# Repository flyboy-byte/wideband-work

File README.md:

# wideband-work: rusEFI wideband controller with a 0-5 V analog output

> [!NOTE]
> This is a fork of [mck1117/wideband](https://github.com/mck1117/wideband) (MIT) on branch `analog-out`. `master` is
> upstream, untouched. Nothing here has been built or tested on hardware yet. As of 2026-10-24 the carrier board (r41)
> is routed and checked, with JLC fab files exported and verified part by part; an independent audit round and the
> order are still to come. **Reviewing it?** Start at [`REVIEW.md`](REVIEW.md).

This repository is three things at once.

**1. A wideband O2 controller.** It is upstream's open STM32 controller for a Bosch LSU 4.9 sensor plus a 0-5 V analog
output on the carrier board. With that output it works with any ECU or logger that reads a voltage, not only rusEFI
over CAN: Speeduino, a Honda K20 on Hondata FlashPro (datalogging), a gauge for carburettor tuning. The output is
10-20 AFR = 0-5 V, 5 V (off-scale lean) while the sensor isn't ready, buffered from a 3.000 V reference and filtered. The op-amp takes
its feedback at the output pin, so the receiver's input (pull-up or pull-down) doesn't shift the reading, and it stays
stable into cable capacitance; both were checked against TI's op-amp model. The firmware also gains an independent
watchdog on the heater loop, and fixes for three bugs found by host and emulator tests: two inherited from upstream
(bootloader write bounds, a Cortex-M0 fault handler that locked up) and one of ours.

**2. An AI-designed hardware project.** Claude (Anthropic) did the design work from code, with the owner directing it:
- the requirements, parts research against the JLC/LCSC catalogue, and the firmware change
- the schematic (`work/gen/gen_carrier_sch.py`) and the PCB (`work/gen/gen_carrier_pcb.py`, with placement, routing and
  a negotiated router for the dense analog area), all generated
- SPICE checks of the analog stage
- the JLC fab files, with each part's rotation, origin and pin names measured from its EasyEDA footprint (that check
  caught the reverse-polarity diode, which would otherwise have been placed backwards)
- every check that gates an order

Every claim carries an evidence tag (DOCUMENTED / REPORTED / INFERRED / UNKNOWN), and the mistakes it caught are in
`work/LESSONS.md`.

**3. A worked example of a documented workflow.** The project follows the
[`pcb-design` skill](https://github.com/flyboy-byte/scripts-docs-dotfiles/tree/master/skills/pcb-design):
- a stage-gated `STATE.md`
- checks that run together (`work/checks/run_all.py`)
- a money gate (`release.py`) that refuses to copy fab files unless everything passes and an audit is clear
- a drift check for hand edits in KiCad
- attempt logs with results
- a `HANDOFF.md`, so a new session or another model can pick the work up cold

`AGENTS.md` is written for any model; Codex audits go through `work/checks/audit_pack.py`, and the two models take
turns (audit, verify, fix) as `AGENTS.md` describes. Rounds so far are in `work/AUDIT.md`. Outside reviewers (a person,
or their own model) start at [`REVIEW.md`](REVIEW.md): setup from a fresh clone, blind pack or full repo, report format.

## Where to look

| Path | What |
| --- | --- |
| `work/STATE.md` | Current stage, decisions, check results, what's open |
| `work/RELEASE_ASSESSMENT.md` | Plain-language status: what is checked, how independently, the open caveats |
| `work/HANDOFF.md` | Dense hand-off for the next session: run history, last raw output, next steps |
| `work/docs/analog-out.md`, `carrier.md`, `firmware.md` | The design, with sources |
| `work/gen/` | Schematic and PCB generators, the routing finisher |
| `work/checks/` | The checks (`run_all.py`): DRC against upstream's baseline, via-in-pad, layout review, JLC rotation, fab files, firmware tests, drift, release gate |
| `work/gen/export_fab.py` | Gerbers, BOM and CPL for JLC (into `work/out/`, gitignored; only `release.py` puts files in `fab/`) |
| `work/sim/` | ngspice decks: filter, op-amp stability, accuracy into different receiver inputs |
| `firmware/` (branch `analog-out`) | Analog output on PB1 / TIM3_CH4, bench test mode, trim, watchdog |
| `test/` | Upstream's unit tests plus ours (`test/aux_out/` for the analog output) |
| `AGENTS.md`, `CLAUDE.md` | How an AI (any model) works in this repo |

---

*Upstream's README follows.*

# rusEFI Wideband Controller

[User Documentation](https://rusefi.com/s/wb)

[Forum Thread](https://rusefi.com/forum/viewtopic.php?f=4&t=1856)

## Building Firmware

The `firmware/boards` directory contains configuration for each board this firmware supports.

For the standalone board and the module built in to rusEFI Hellen boards, `f0_module` is the correct target.  Use the `build_wideband.sh` script to build and package the wideband firmware: both a bin including the bootloader, and a header file consumed by rusEFI that contains no bootloader, to be uploaded over CAN (via the aforementioned bootloader).

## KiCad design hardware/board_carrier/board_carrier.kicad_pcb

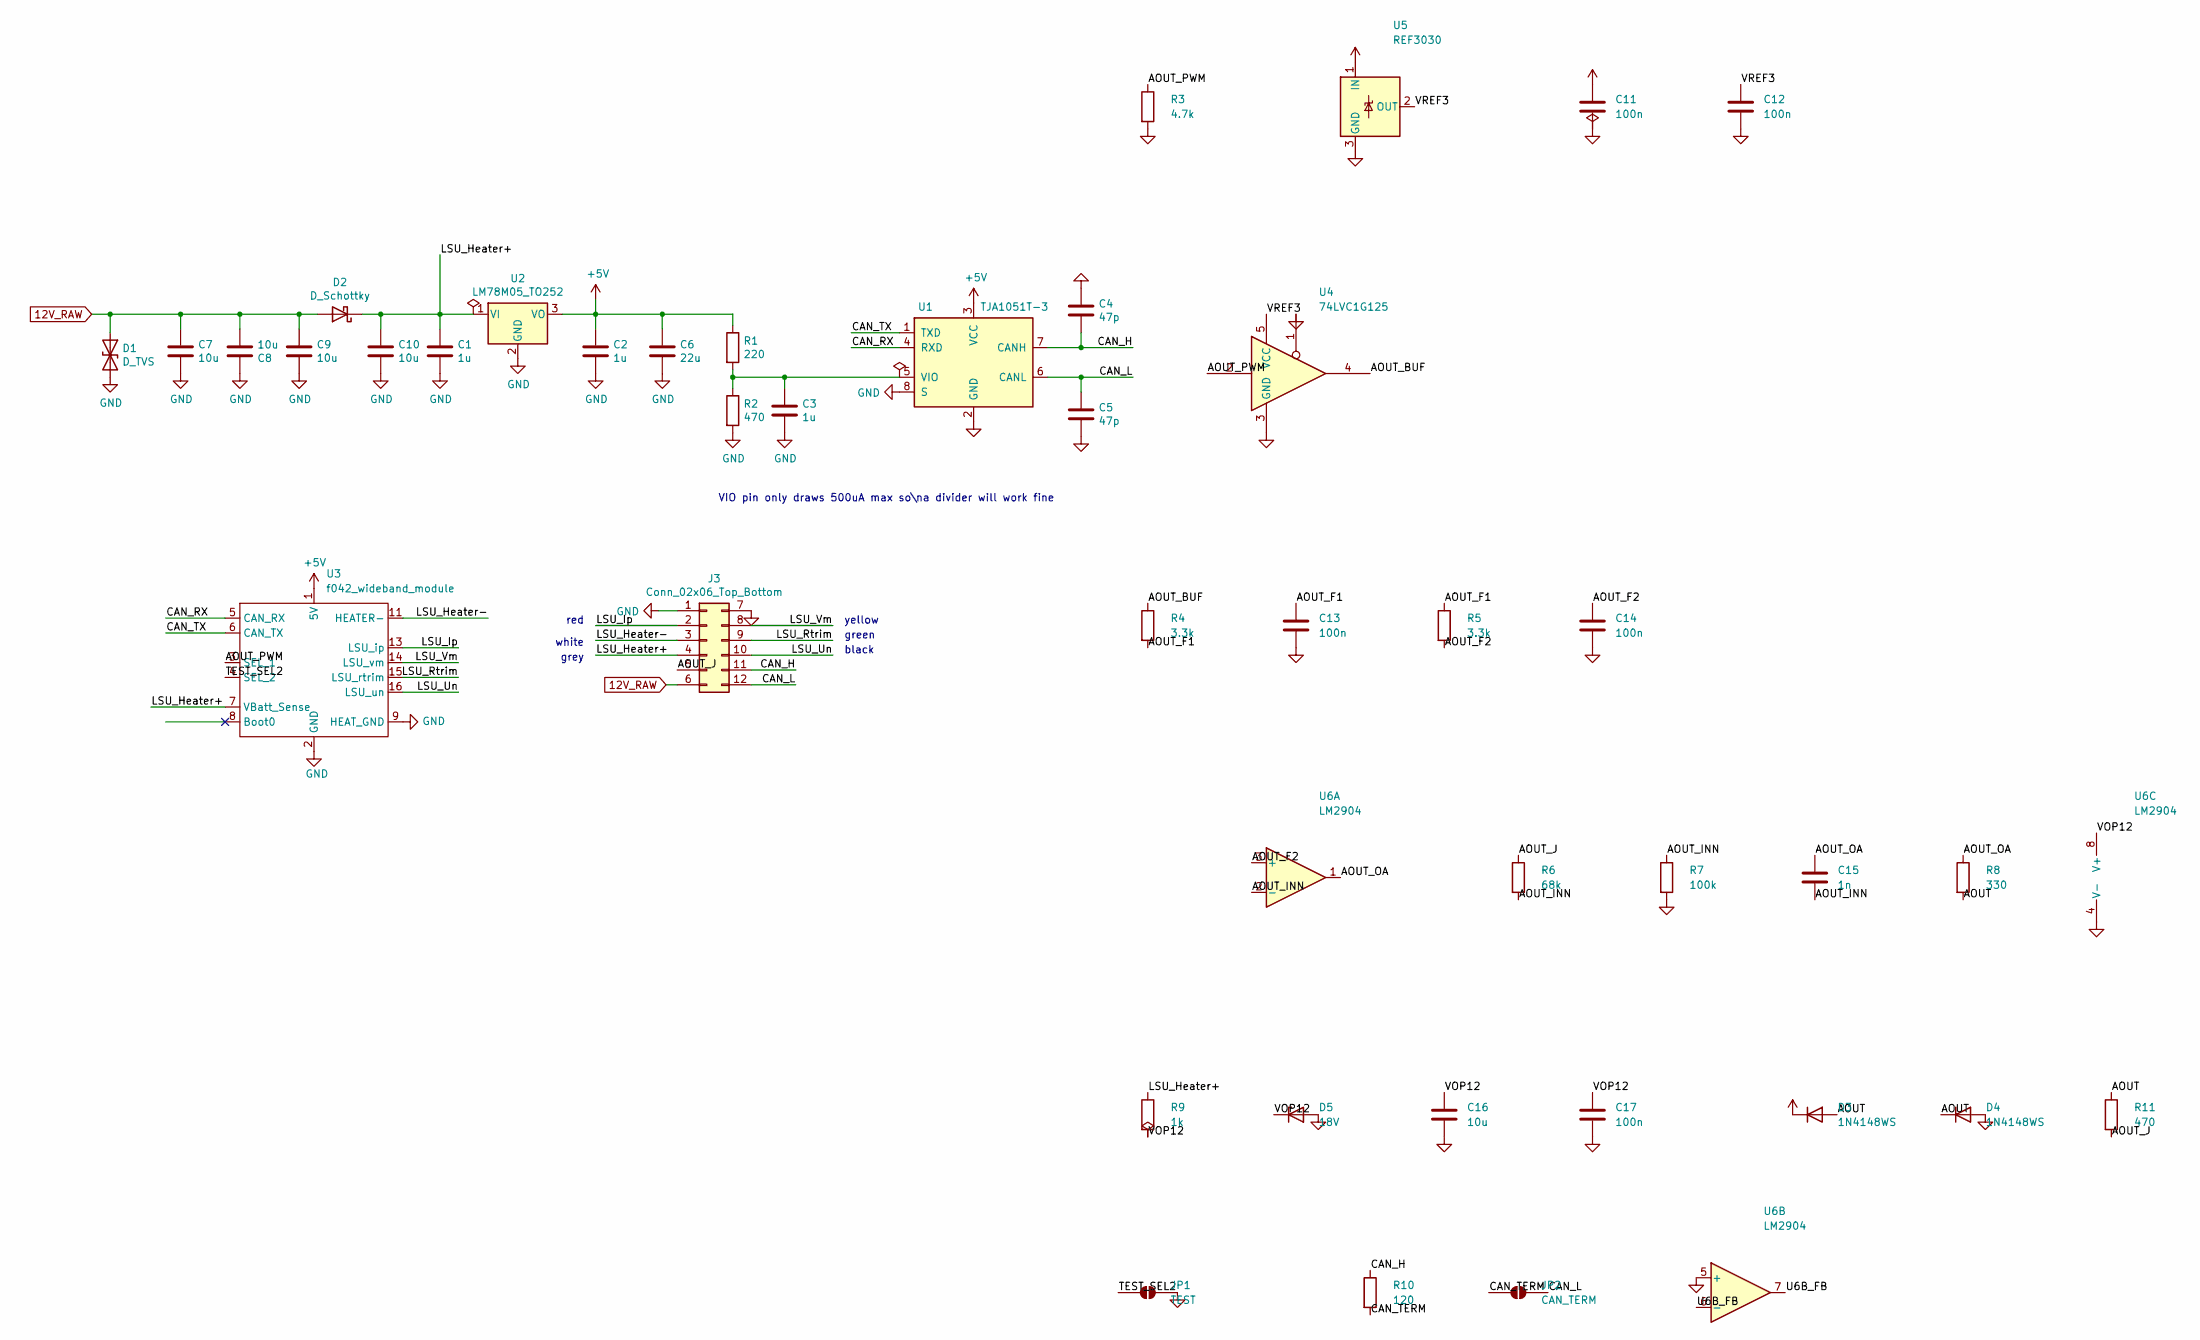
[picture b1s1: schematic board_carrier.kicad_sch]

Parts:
C1, C2, C3: 1u; C_0603_1608Metric; LCSC C15849
C4, C5: 47p; C_0402_1005Metric; LCSC C1567
C6: 22u; C_0805_2012Metric; LCSC C45783
C7, C8, C9, C10, C16: 10u; C_1206_3216Metric; LCSC C13585
C11, C12, C13, C14: 100n; C_0402_1005Metric; LCSC C1525
C15: 1n; C_0402_1005Metric; LCSC C1523
C17: 100n; C_0603_1608Metric; LCSC C14663
D1: D_TVS; D_SMC; LCSC C151279
D2: D_Schottky; D_SMA; LCSC C22452
D3, D4: 1N4148WS; D_SOD-323; LCSC C2128
D5: 18V; D_SOD-123; LCSC C173425
J3: Conn_02x06_Top_Bottom; mx120g-12
JP1: TEST; SolderJumper-2_P1.3mm_Open_RoundedPad1.0x1.5mm
JP2: CAN_TERM; SolderJumper-2_P1.3mm_Open_RoundedPad1.0x1.5mm
R1: 220; R_0603_1608Metric; LCSC C22962
R2: 470; R_0603_1608Metric; LCSC C23179
R3: 4.7k; R_0402_1005Metric; LCSC C25900
R4, R5: 3.3k; R_0402_1005Metric; LCSC C25890
R6: 68k; R_0603_1608Metric; LCSC C23231
R7: 100k; R_0402_1005Metric; LCSC C25741
R8: 330; R_0603_1608Metric; LCSC C23138
R9: 1k; R_1206_3216Metric; LCSC C844867
R10: 120; R_0402_1005Metric; LCSC C25079
R11: 470; R_1206_3216Metric; LCSC C4502
U1: TJA1051T-3; SOIC-8_3.9x4.9mm_P1.27mm; LCSC C38695
U2: LM78M05_TO252; TO-252-2; LCSC C58069
U3: f042_wideband_module
U4: 74LVC1G125; SOT-353_SC-70-5; LCSC C12519
U5: REF3030; SOT-23; LCSC C38423
U6: LM2904; SOIC-8_3.9x4.9mm_P1.27mm; LCSC C7934

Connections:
12V_RAW: C7.1, C8.2, C9.1, D1.1 (A1), D2.2 (A), J3.6
+5V: C2.1, C6.1, C11.1, D3.1 (K), R1.1, U1.3 (VCC), U2.3 (VO), U3.1 (5V), U5.1 (IN)
/AOUT: D3.2 (A), D4.1 (K), R8.2, R11.1
/AOUT_BUF: R4.1, U4.4
/AOUT_F1: C13.1, R4.2, R5.1
/AOUT_F2: C14.1, R5.2, U6.3 (+)
/AOUT_INN: C15.2, R6.2, R7.1, U6.2 (-)
/AOUT_J: J3.5, R6.1, R11.2
/AOUT_OA: C15.1, R8.1, U6.1
/AOUT_PWM: R3.1, U3.3 (SEL_1), U4.2
/CAN_H: C4.2, J3.11, R10.1, U1.7 (CANH)
/CAN_L: C5.1, J3.12, JP2.2 (B), U1.6 (CANL)
/CAN_RX: U1.4 (RXD), U3.5 (CAN_RX)
/CAN_TERM: JP2.1 (A), R10.2
/CAN_TX: U1.1 (TXD), U3.6 (CAN_TX)
/LSU_Heater+: C1.1, C10.1, D2.1 (K), J3.4, R9.1, U2.1 (VI), U3.7 (VBatt_Sense)
/LSU_Heater-: J3.3, U3.11 (HEATER-), U3.12 (HEATER-)
/LSU_Ip: J3.2, U3.13 (LSU_ip)
/LSU_Rtrim: J3.9, U3.15 (LSU_rtrim)
/LSU_Un: J3.10, U3.16 (LSU_un)
/LSU_Vm: J3.8, U3.14 (LSU_vm)
/TEST_SEL2: JP1.1 (A), U3.4 (SEL_2)
/U6B_FB: U6.6 (-), U6.7
/VOP12: C16.1, C17.1, D5.1 (K), R9.2, U6.8 (V+)
/VREF3: C12.1, U4.5 (VCC), U5.2 (OUT)
GND: C1.2, C2.2, C3.2, C4.1, C5.2, C6.2, C7.2, C8.1, C9.2, C10.2, C11.2, C12.2, C13.2, C14.2, C16.2, C17.2, D1.2 (A2), D4.2 (A), D5.2 (A), J3.1, J3.7, JP1.2 (B), R2.2, R3.2, R7.2, U1.2 (GND), U1.8 (S), U2.2 (GND), U3.2 (GND), U3.9 (HEAT_GND), U3.10 (HEAT_GND2), U4.1, U4.3 (GND), U5.3 (GND), U6.4 (V-), U6.5 (+)
unnamed: C3.1, R1.2, R2.1, U1.5 (VIO)

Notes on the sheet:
yellow
green
red
black
white
VIO pin only draws 500uA max so\na divider will work fine
grey

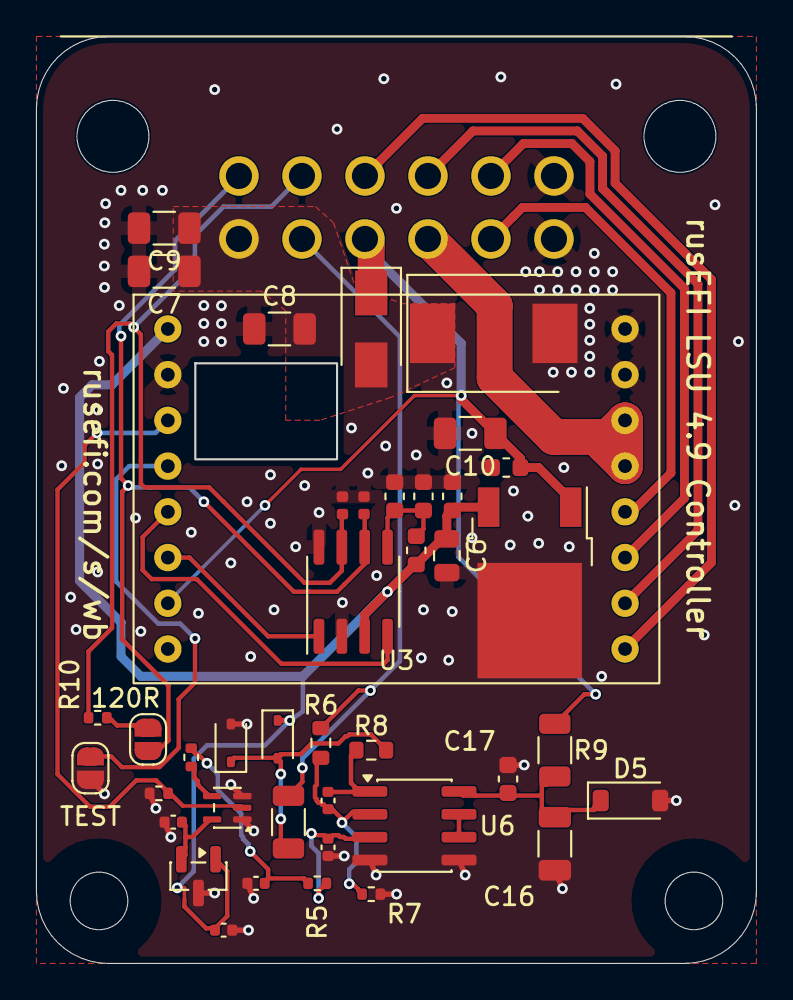
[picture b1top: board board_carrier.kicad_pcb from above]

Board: 2 copper layers, 40.0 x 51.5 mm, 44 parts (0 on the bottom side), 27 nets.

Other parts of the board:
H1, H2: MountingHole_3.2mm_M3
